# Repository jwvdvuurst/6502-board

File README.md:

# 6502-board

A W65C02S computer board with bank-switched SRAM, a ROM monitor and Tiny BASIC,
and a Raspberry Pi Pico USB terminal bridge.

- [Board design and hardware status](DESIGN.md)
- [ROM build, monitor commands, and BASIC](firmware/README.md)
- [Pico C firmware, build, and wiring](pico/README.md)
- [ROM/Pico interface contract](firmware/PROTOCOL.md)
- [Electrical schematic PDF](6502-electrical-draft.pdf)

The hardware is an electrical draft, not fabrication-ready. ROM firmware has
been tested in emulation. Pico C firmware builds to UF2 and passes portable
tests; physical hardware and USB/GPIO integration remain to be validated.

# Agents

Agents must follow the rules, references, skills and agents described in the [AI-hub](C:\Users\JWvdV\Documents\workspace\AI-hub) when this is available.
See also [AGENTS.md](AGENTS.md).

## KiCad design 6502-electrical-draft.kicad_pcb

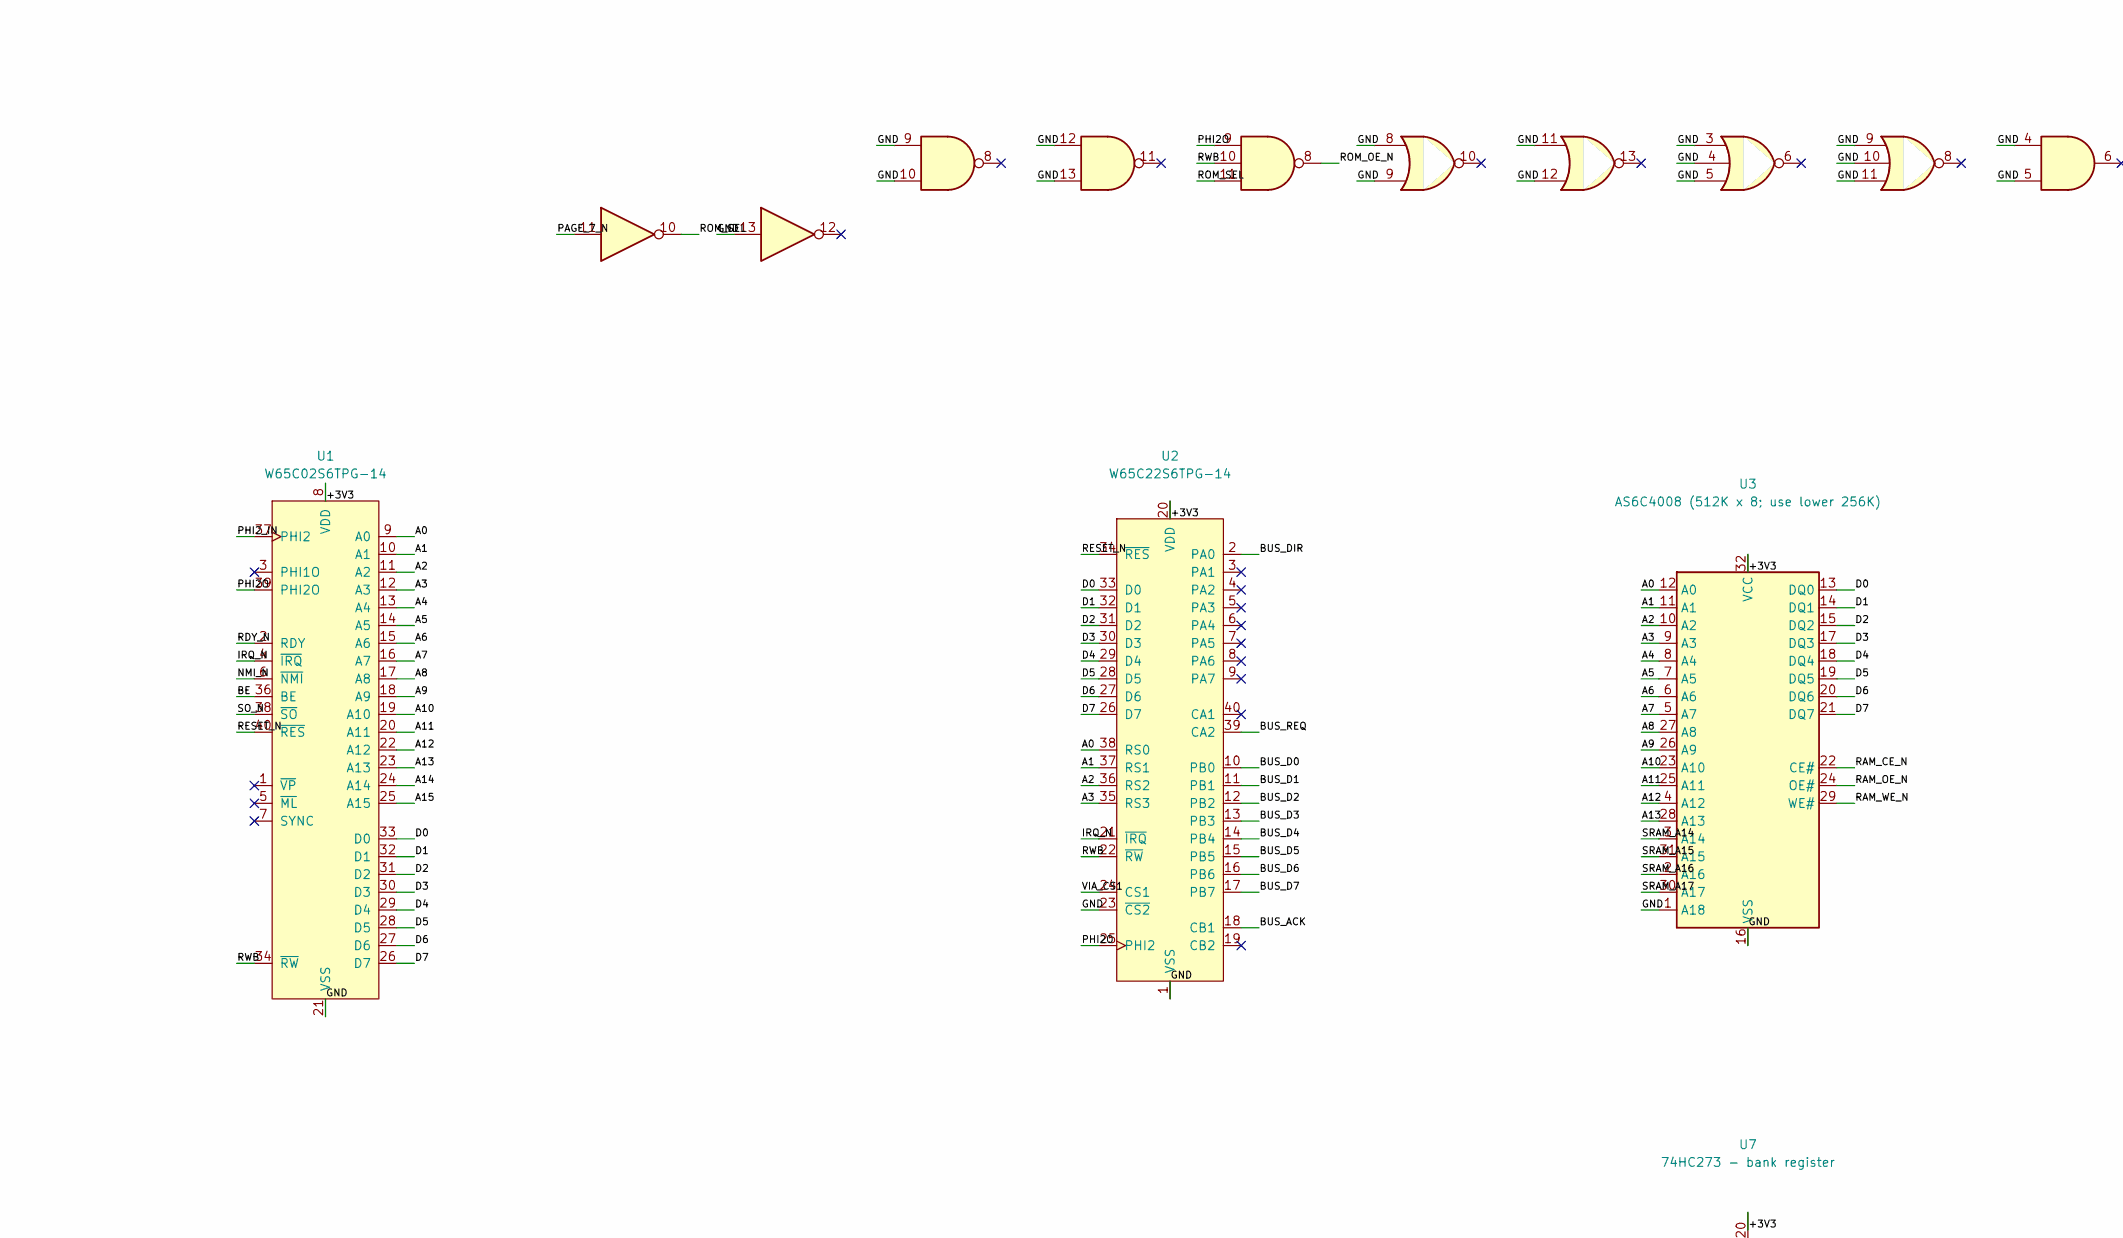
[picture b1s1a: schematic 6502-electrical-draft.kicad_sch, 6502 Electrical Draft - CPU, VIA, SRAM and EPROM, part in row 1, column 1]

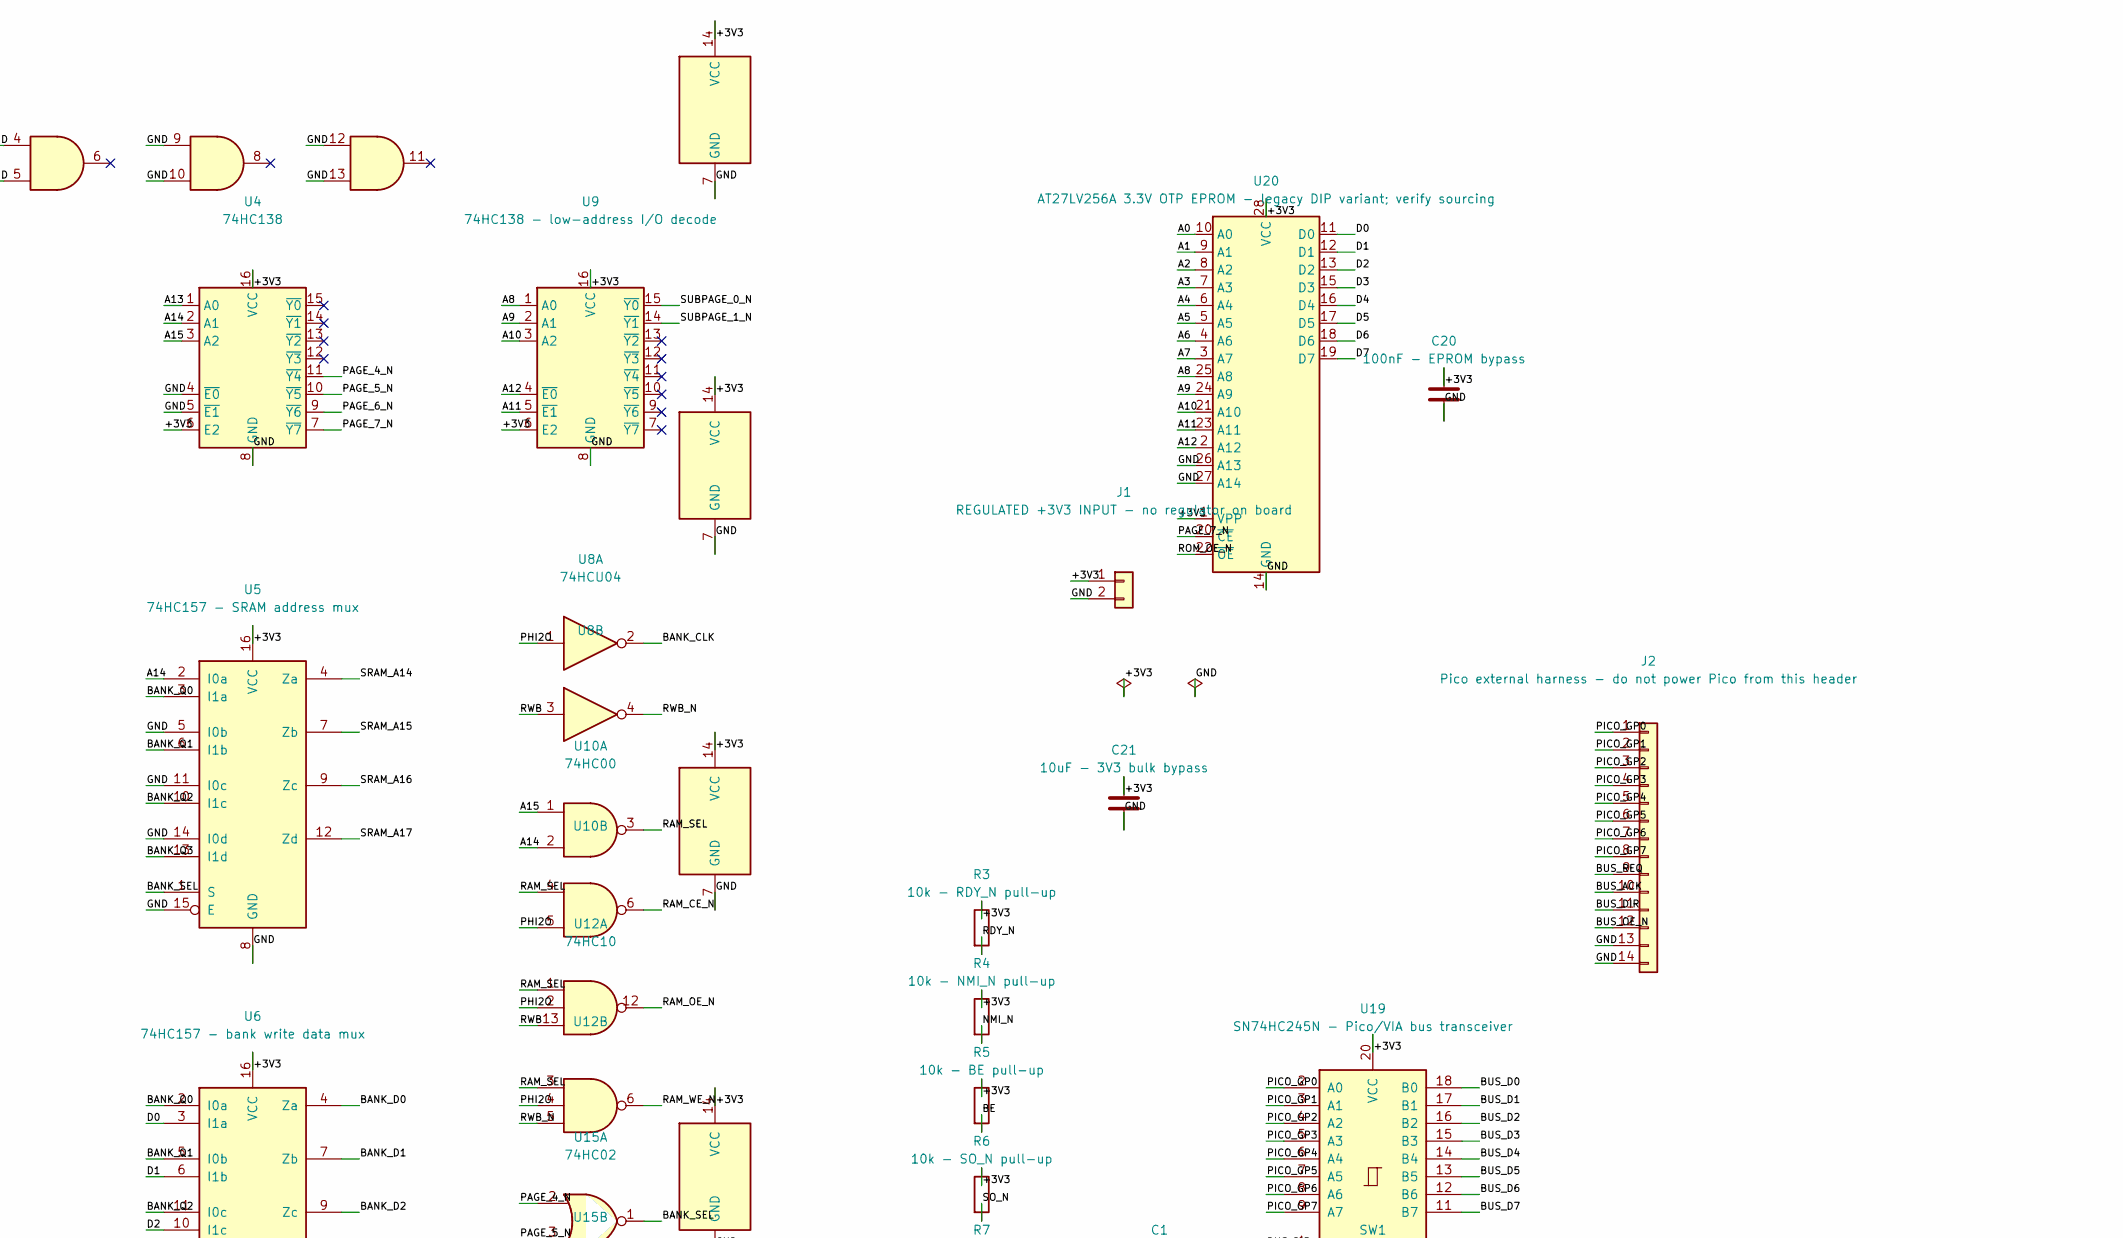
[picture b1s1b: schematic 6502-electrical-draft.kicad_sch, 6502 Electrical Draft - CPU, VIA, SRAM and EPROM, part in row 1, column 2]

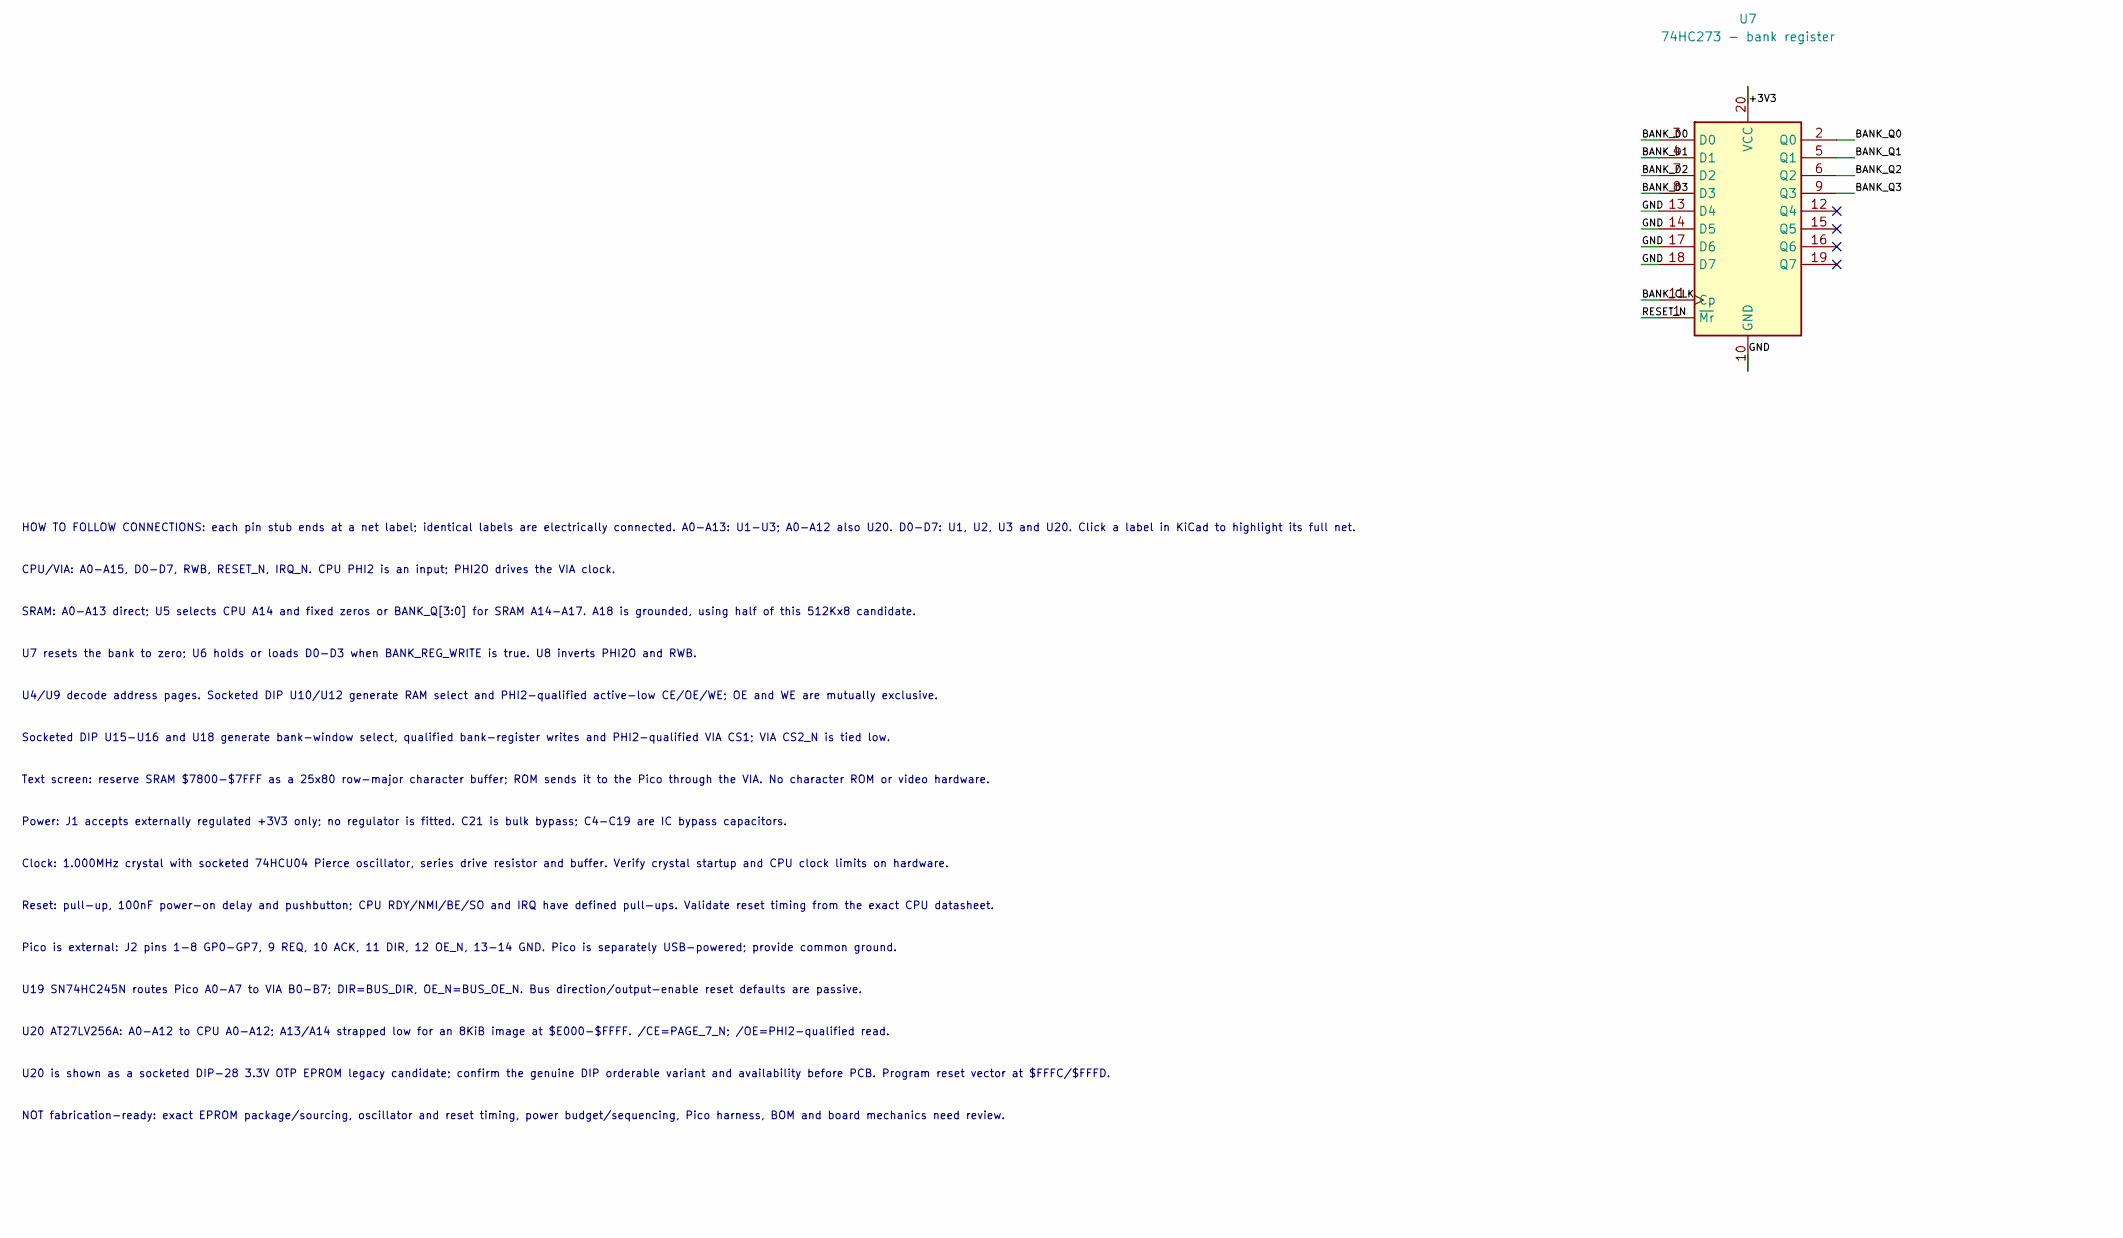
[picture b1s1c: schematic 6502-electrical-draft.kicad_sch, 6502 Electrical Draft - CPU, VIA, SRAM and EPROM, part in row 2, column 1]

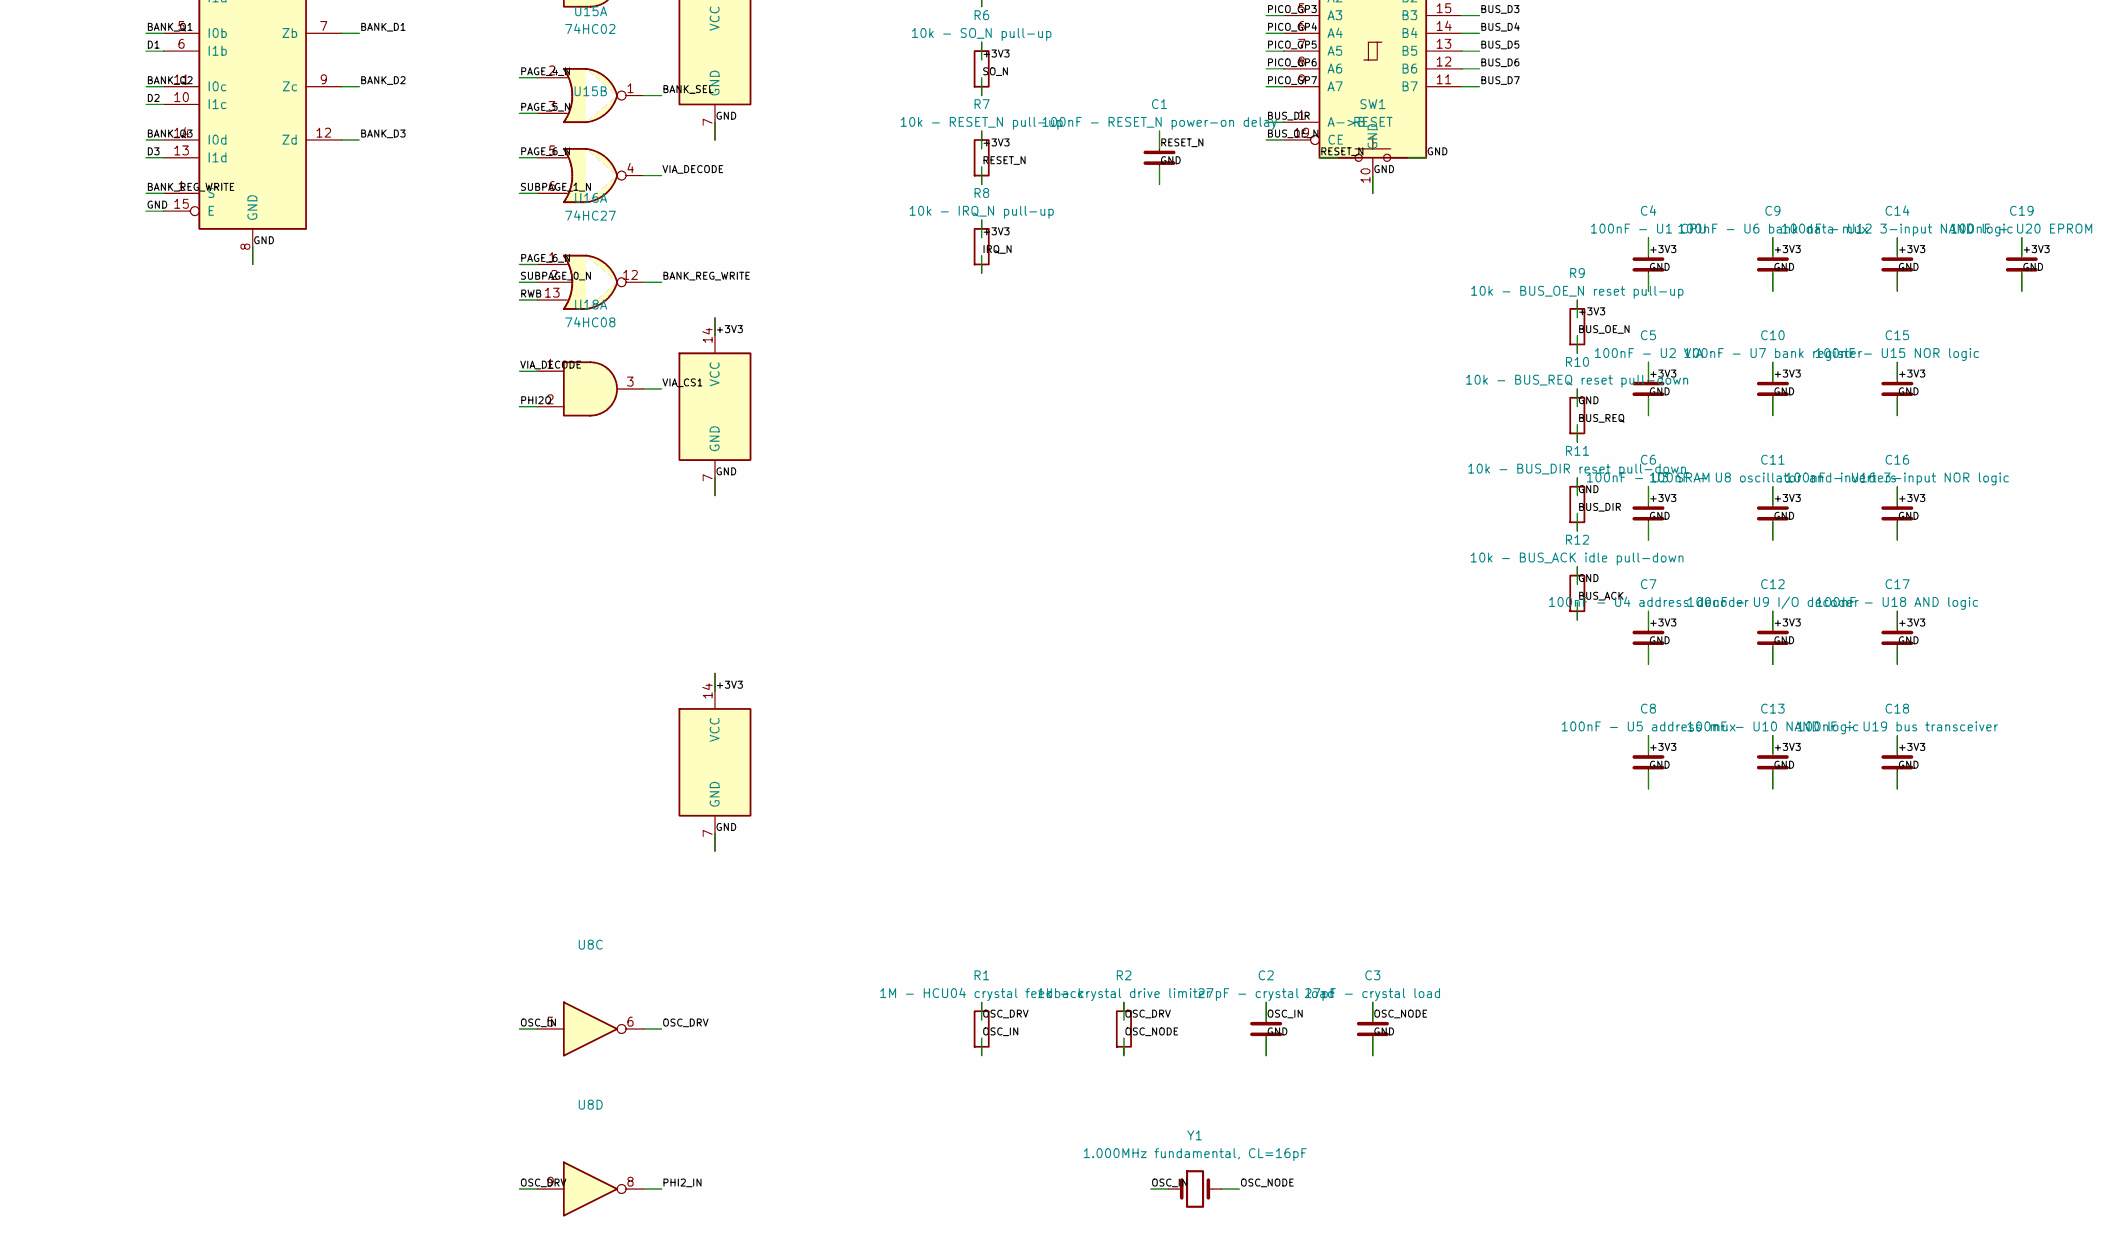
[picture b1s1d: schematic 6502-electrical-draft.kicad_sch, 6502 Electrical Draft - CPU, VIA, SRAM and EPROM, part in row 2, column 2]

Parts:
C1: 100nF - RESET_N power-on delay; C_Disc_D5.0mm_W2.5mm_P5.00mm
C2, C3: 27pF - crystal load; C_Disc_D5.0mm_W2.5mm_P5.00mm
C4: 100nF - U1 CPU; C_Disc_D5.0mm_W2.5mm_P5.00mm
C5: 100nF - U2 VIA; C_Disc_D5.0mm_W2.5mm_P5.00mm
C6: 100nF - U3 SRAM; C_Disc_D5.0mm_W2.5mm_P5.00mm
C7: 100nF - U4 address decoder; C_Disc_D5.0mm_W2.5mm_P5.00mm
C8: 100nF - U5 address mux; C_Disc_D5.0mm_W2.5mm_P5.00mm
C9: 100nF - U6 bank data mux; C_Disc_D5.0mm_W2.5mm_P5.00mm
C10: 100nF - U7 bank register; C_Disc_D5.0mm_W2.5mm_P5.00mm
C11: 100nF - U8 oscillator and inverters; C_Disc_D5.0mm_W2.5mm_P5.00mm
C12: 100nF - U9 I/O decoder; C_Disc_D5.0mm_W2.5mm_P5.00mm
C13: 100nF - U10 NAND logic; C_Disc_D5.0mm_W2.5mm_P5.00mm
C14: 100nF - U12 3-input NAND logic; C_Disc_D5.0mm_W2.5mm_P5.00mm
C15: 100nF - U15 NOR logic; C_Disc_D5.0mm_W2.5mm_P5.00mm
C16: 100nF - U16 3-input NOR logic; C_Disc_D5.0mm_W2.5mm_P5.00mm
C17: 100nF - U18 AND logic; C_Disc_D5.0mm_W2.5mm_P5.00mm
C18: 100nF - U19 bus transceiver; C_Disc_D5.0mm_W2.5mm_P5.00mm
C19: 100nF - U20 EPROM; C_Disc_D5.0mm_W2.5mm_P5.00mm
C20: 100nF - EPROM bypass; C_Disc_D5.0mm_W2.5mm_P5.00mm
C21: 10uF - 3V3 bulk bypass; C_Disc_D5.0mm_W2.5mm_P5.00mm
J1: REGULATED +3V3 INPUT - no regulator on board; PinHeader_1x02_P2.54mm_Vertical
J2: Pico external harness - do not power Pico from th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; PinHeader_1x14_P2.54mm_Vertical
R1: 1M - HCU04 crystal feedback; R_Axial_DIN0207_L6.3mm_D2.5mm_P7.62mm_Horizontal
R2: 1k - crystal drive limiter; R_Axial_DIN0207_L6.3mm_D2.5mm_P7.62mm_Horizontal
R3: 10k - RDY_N pull-up; R_Axial_DIN0207_L6.3mm_D2.5mm_P7.62mm_Horizontal
R4: 10k - NMI_N pull-up; R_Axial_DIN0207_L6.3mm_D2.5mm_P7.62mm_Horizontal
R5: 10k - BE pull-up; R_Axial_DIN0207_L6.3mm_D2.5mm_P7.62mm_Horizontal
R6: 10k - SO_N pull-up; R_Axial_DIN0207_L6.3mm_D2.5mm_P7.62mm_Horizontal
R7: 10k - RESET_N pull-up; R_Axial_DIN0207_L6.3mm_D2.5mm_P7.62mm_Horizontal
R8: 10k - IRQ_N pull-up; R_Axial_DIN0207_L6.3mm_D2.5mm_P7.62mm_Horizontal
R9: 10k - BUS_OE_N reset pull-up; R_Axial_DIN0207_L6.3mm_D2.5mm_P7.62mm_Horizontal
R10: 10k - BUS_REQ reset pull-down; R_Axial_DIN0207_L6.3mm_D2.5mm_P7.62mm_Horizontal
R11: 10k - BUS_DIR reset pull-down; R_Axial_DIN0207_L6.3mm_D2.5mm_P7.62mm_Horizontal
R12: 10k - BUS_ACK idle pull-down; R_Axial_DIN0207_L6.3mm_D2.5mm_P7.62mm_Horizontal
SW1: RESET; SW_PUSH_6mm
U1: W65C02S6TPG-14; DIP-40_W15.24mm_Socket
U2: W65C22S6TPG-14; DIP-40_W15.24mm_Socket
U3: AS6C4008 (512K x 8; use lower 256K); DIP-32_W15.24mm_Socket
U4: 74HC138; DIP-16_W7.62mm_Socket
U5: 74HC157 - SRAM address mux; DIP-16_W7.62mm_Socket
U6: 74HC157 - bank write data mux; DIP-16_W7.62mm_Socket
U7: 74HC273 - bank register; DIP-20_W7.62mm_Socket
U8: 74HCU04; DIP-14_W7.62mm_Socket
U9: 74HC138 - low-address I/O decode; DIP-16_W7.62mm_Socket
U10: 74HC00; DIP-14_W7.62mm_Socket
U12: 74HC10; DIP-14_W7.62mm_Socket
U15: 74HC02; DIP-14_W7.62mm_Socket
U16: 74HC27; DIP-14_W7.62mm_Socket
U18: 74HC08; DIP-14_W7.62mm_Socket
U19: SN74HC245N - Pico/VIA bus transceiver; DIP-20_W7.62mm_Socket
U20: AT27LV256A 3.3V OTP EPROM - legacy DIP variant; v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; DIP-28_W15.24mm_Socket
Y1: 1.000MHz fundamental, CL=16pF; Crystal_HC49-U_Vertical

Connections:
/+3V3: C4.1, C5.1, C6.1, C7.1, C8.1, C9.1, C10.1, C11.1, C12.1, C13.1, C14.1, C15.1, C16.1, C17.1, C18.1, C19.1, C20.1, C21.1, J1.1, R3.1, R4.1, R5.1, R6.1, R7.1, R8.1, R9.1, U1.8 (VDD), U2.20 (VDD), U3.32 (VCC), U4.6 (E2), U4.16 (VCC), U5.16 (VCC), U6.16 (VCC), U7.20 (VCC), U8.14 (VCC), U9.6 (E2), U9.16 (VCC), U10.14 (VCC), U12.14 (VCC), U15.14 (VCC), U16.14 (VCC), U18.14 (VCC), U19.20 (VCC), U20.1 (VPP), U20.28 (VCC)
/A0: U1.9 (A0), U2.38 (RS0), U3.12 (A0), U20.10 (A0)
/A1: U1.10 (A1), U2.37 (RS1), U3.11 (A1), U20.9 (A1)
/A2: U1.11 (A2), U2.36 (RS2), U3.10 (A2), U20.8 (A2)
/A3: U1.12 (A3), U2.35 (RS3), U3.9 (A3), U20.7 (A3)
/A4: U1.13 (A4), U3.8 (A4), U20.6 (A4)
/A5: U1.14 (A5), U3.7 (A5), U20.5 (A5)
/A6: U1.15 (A6), U3.6 (A6), U20.4 (A6)
/A7: U1.16 (A7), U3.5 (A7), U20.3 (A7)
/A8: U1.17 (A8), U3.27 (A8), U9.1 (A0), U20.25 (A8)
/A9: U1.18 (A9), U3.26 (A9), U9.2 (A1), U20.24 (A9)
/A10: U1.19 (A10), U3.23 (A10), U9.3 (A2), U20.21 (A10)
/A11: U1.20 (A11), U3.25 (A11), U9.5 (~E1), U20.23 (A11)
/A12: U1.22 (A12), U3.4 (A12), U9.4 (~E0), U20.2 (A12)
/A13: U1.23 (A13), U3.28 (A13), U4.1 (A0)
/A14: U1.24 (A14), U4.2 (A1), U5.2 (I0a), U10.2
/A15: U1.25 (A15), U4.3 (A2), U10.1
/BANK_CLK: U7.11 (Cp), U8.2
/BANK_D0: U6.4 (Za), U7.3 (D0)
/BANK_D1: U6.7 (Zb), U7.4 (D1)
/BANK_D2: U6.9 (Zc), U7.7 (D2)
/BANK_D3: U6.12 (Zd), U7.8 (D3)
/BANK_Q0: U5.3 (I1a), U6.2 (I0a), U7.2 (Q0)
/BANK_Q1: U5.6 (I1b), U6.5 (I0b), U7.5 (Q1)
/BANK_Q2: U5.10 (I1c), U6.11 (I0c), U7.6 (Q2)
/BANK_Q3: U5.13 (I1d), U6.14 (I0d), U7.9 (Q3)
/BANK_REG_WRITE: U6.1 (S), U16.12
/BANK_SEL: U5.1 (S), U15.1
/BE: R5.2, U1.36 (BE)
/BUS_ACK: J2.10, R12.2, U2.18 (CB1)
/BUS_D0: U2.10 (PB0), U19.18 (B0)
/BUS_D1: U2.11 (PB1), U19.17 (B1)
/BUS_D2: U2.12 (PB2), U19.16 (B2)
/BUS_D3: U2.13 (PB3), U19.15 (B3)
/BUS_D4: U2.14 (PB4), U19.14 (B4)
/BUS_D5: U2.15 (PB5), U19.13 (B5)
/BUS_D6: U2.16 (PB6), U19.12 (B6)
/BUS_D7: U2.17 (PB7), U19.11 (B7)
/BUS_DIR: J2.11, R11.2, U2.2 (PA0), U19.1 (A->B)
/BUS_OE_N: J2.12, R9.2, U19.19 (CE)
/BUS_REQ: J2.9, R10.2, U2.39 (CA2)
/D0: U1.33 (D0), U2.33 (D0), U3.13 (DQ0), U6.3 (I1a), U20.11 (D0)
/D1: U1.32 (D1), U2.32 (D1), U3.14 (DQ1), U6.6 (I1b), U20.12 (D1)
/D2: U1.31 (D2), U2.31 (D2), U3.15 (DQ2), U6.10 (I1c), U20.13 (D2)
/D3: U1.30 (D3), U2.30 (D3), U3.17 (DQ3), U6.13 (I1d), U20.15 (D3)
/D4: U1.29 (D4), U2.29 (D4), U3.18 (DQ4), U20.16 (D4)
/D5: U1.28 (D5), U2.28 (D5), U3.19 (DQ5), U20.17 (D5)
/D6: U1.27 (D6), U2.27 (D6), U3.20 (DQ6), U20.18 (D6)
/D7: U1.26 (D7), U2.26 (D7), U3.21 (DQ7), U20.19 (D7)
/GND: C1.2, C2.2, C3.2, C4.2, C5.2, C6.2, C7.2, C8.2, C9.2, C10.2, C11.2, C12.2, C13.2, C14.2, C15.2, C16.2, C17.2, C18.2, C19.2, C20.2, C21.2, J1.2, J2.13, J2.14, R10.1, R11.1, R12.1, SW1.2, U1.21 (VSS), U2.1 (VSS), U2.23 (~CS2), U3.1 (A18), U3.16 (VSS), U4.4 (~E0), U4.5 (~E1), U4.8 (GND), U5.5 (I0b), U5.8 (GND), U5.11 (I0c), U5.14 (I0d), U5.15 (E), U6.8 (GND), U6.15 (E), U7.10 (GND), U7.13 (D4), U7.14 (D5), U7.17 (D6), U7.18 (D7), U8.7 (GND), U8.13, U9.8 (GND), U10.7 (GND), U10.9, U10.10, U10.12, U10.13, U12.7 (GND), U15.7 (GND), U15.8, U15.9, U15.11, U15.12, U16.3, U16.4, U16.5, U16.7 (GND), U16.9, U16.10, U16.11, U18.4, U18.5, U18.7 (GND), U18.9, U18.10, U18.12, U18.13, U19.10 (GND), U20.14 (GND), U20.26 (A13), U20.27 (A14)
/IRQ_N: R8.2, U1.4 (~IRQ), U2.21 (~IRQ)
/NMI_N: R4.2, U1.6 (~NMI)
/OSC_DRV: R1.1, R2.1, U8.6, U8.9
/OSC_IN: C2.1, R1.2, U8.5, Y1.1
/OSC_NODE: C3.1, R2.2, Y1.2
/PAGE_4_N: U4.11 (~Y4), U15.2
/PAGE_5_N: U4.10 (~Y5), U15.3
/PAGE_6_N: U4.9 (~Y6), U15.5, U16.1
/PAGE_7_N: U4.7 (~Y7), U8.11, U20.20 (~CE)
/PHI2O: U1.39 (PHI2O), U2.25 (PHI2), U8.1, U10.5, U12.2, U12.4, U12.9, U18.2
/PHI2_IN: U1.37 (PHI2), U8.8
/PICO_GP0: J2.1, U19.2 (A0)
/PICO_GP1: J2.2, U19.3 (A1)
/PICO_GP2: J2.3, U19.4 (A2)
/PICO_GP3: J2.4, U19.5 (A3)
/PICO_GP4: J2.5, U19.6 (A4)
/PICO_GP5: J2.6, U19.7 (A5)
/PICO_GP6: J2.7, U19.8 (A6)
/PICO_GP7: J2.8, U19.9 (A7)
/RAM_CE_N: U3.22 (CE#), U10.6
/RAM_OE_N: U3.24 (OE#), U12.12
/RAM_SEL: U10.3, U10.4, U12.1, U12.3
/RAM_WE_N: U3.29 (WE#), U12.6
/RDY_N: R3.2, U1.2 (RDY)
/RESET_N: C1.1, R7.2, SW1.1, U1.40 (~RES), U2.34 (~RES), U7.1 (~Mr)
/ROM_OE_N: U12.8, U20.22 (~OE)
/ROM_SEL: U8.10, U12.11
/RWB: U1.34 (~RW), U2.22 (~RW), U8.3, U12.10, U12.13, U16.13
/RWB_N: U8.4, U12.5
/SO_N: R6.2, U1.38 (~SO)
/SRAM_A14: U3.3 (A14), U5.4 (Za)
/SRAM_A15: U3.31 (A15), U5.7 (Zb)
/SRAM_A16: U3.2 (A16), U5.9 (Zc)
/SRAM_A17: U3.30 (A17), U5.12 (Zd)
/SUBPAGE_0_N: U9.15 (~Y0), U16.2
/SUBPAGE_1_N: U9.14 (~Y1), U15.6
/VIA_CS1: U2.24 (CS1), U18.3
/VIA_DECODE: U15.4, U18.1

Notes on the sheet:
HOW TO FOLLOW CONNECTIONS: each pin stub ends at a net label; identical labels are electrically connected. A0-A13: U1-U3; A0-A12 also U20. D0-D7: U1, U2, U3 and U20. Click a label in KiCad to highlight its full net.
CPU/VIA: A0-A15, D0-D7, RWB, RESET_N, IRQ_N. CPU PHI2 is an input; PHI2O drives the VIA clock.
SRAM: A0-A13 direct; U5 selects CPU A14 and fixed zeros or BANK_Q[3:0] for SRAM A14-A17. A18 is grounded, using half of this 512Kx8 candidate.
U7 resets the bank to zero; U6 holds or loads D0-D3 when BANK_REG_WRITE is true. U8 inverts PHI2O and RWB.
U4/U9 decode address pages. Socketed DIP U10/U12 generate RAM select and PHI2-qualified active-low CE/OE/WE; OE and WE are mutually exclusive.
Socketed DIP U15-U16 and U18 generate bank-window select, qualified bank-register writes and PHI2-qualified VIA CS1; VIA CS2_N is tied low.
Text screen: reserve SRAM $7800-$7FFF as a 25x80 row-major character buffer; ROM sends it to the Pico through the VIA. No character ROM or video hardware.
Power: J1 accepts externally regulated +3V3 only; no regulator is fitted. C21 is bulk bypass; C4-C19 are IC bypass capacitors.
Clock: 1.000MHz crystal with socketed 74HCU04 Pierce oscillator, series drive resistor and buffer. Verify crystal startup and CPU clock limits on hardware.
Reset: pull-up, 100nF power-on delay and pushbutton; CPU RDY/NMI/BE/SO and IRQ have defined pull-ups. Validate reset timing from the exact CPU datasheet.
Pico is external: J2 pins 1-8 GP0-GP7, 9 REQ, 10 ACK, 11 DIR, 12 OE_N, 13-14 GND. Pico is separately USB-powered; provide common ground.
U19 SN74HC245N routes Pico A0-A7 to VIA B0-B7; DIR=BUS_DIR, OE_N=BUS_OE_N. Bus direction/output-enable reset defaults are passive.
U20 AT27LV256A: A0-A12 to CPU A0-A12; A13/A14 strapped low for an 8KiB image at $E000-$FFFF. /CE=PAGE_7_N; /OE=PHI2-qualified read.
U20 is shown as a socketed DIP-28 3.3V OTP EPROM legacy candidate; confirm the genuine DIP orderable variant and availability before PCB. Program reset vector at $FFFC/$FFFD.
NOT fabrication-ready: exact EPROM package/sourcing, oscillator and reset timing, power budget/sequencing, Pico harness, BOM and board mechanics need review.

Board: 2 copper layers, 53 parts (0 on the bottom side), 88 nets, no tracks yet.

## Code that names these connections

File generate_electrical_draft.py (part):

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        "~{RES}": "RESET_N",
        "CA2": "BUS_REQ",
        "CB1": "BUS_ACK",
        "PA0": "BUS_DIR",
        "CA1": None,
        "CB2": None,
        **{f"PA{i}": None for i in range(1, 8)},
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
logic_units = [
    ("74HCU04", "U8", 1, logic_x, 88.9, "BANK_CLK inverter", {
        "PIN1": "PHI2O", "PIN2": "BANK_CLK",
    }),
    ("74HCU04", "U8", 2, logic_x, 99.06, "RWB inverter", {
        "PIN3": "RWB", "PIN4": "RWB_N",
    }),
    ("74HCU04", "U8", 3, 388.62, 304.8, "1 MHz crystal oscillator", {
        "PIN5": "OSC_IN", "PIN6": "OSC_DRV",
    }),
    ("74HCU04", "U8", 4, 388.62, 327.66, "PHI2 clock buffer", {
        "PIN9": "OSC_DRV", "PIN8": "PHI2_IN",
    }),
    ("74HC00", "U10", 1, logic_x, 115.57, "RAM range", {
        "PIN1": "A15", "PIN2": "A14", "PIN3": "RAM_SEL",
    }),
    ("74HC00", "U10", 2, logic_x, 127.0, "RAM /CE", {
        "PIN4": "RAM_SEL", "PIN5": "PHI2O", "PIN6": "RAM_CE_N",
    }),
    ("74HC10", "U12", 1, logic_x, 140.97, "RAM /OE", {
        "PIN1": "RAM_SEL", "PIN2": "PHI2O", "PIN13": "RWB", "PIN12": "RAM_OE_N",
    }),
    ("74HC10", "U12", 2, logic_x, 154.94, "RAM /WE", {
        "PIN3": "RAM_SEL", "PIN4": "PHI2O", "PIN5": "RWB_N", "PIN6": "RAM_WE_N",
    }),
    ("74HC02", "U15", 1, logic_x, 171.45, "bank-window select", {
        "PIN1": "BANK_SEL", "PIN2": "PAGE_4_N", "PIN3": "PAGE_5_N",
    }),
    ("74HC02", "U15", 2, logic_x, 182.88, "VIA address select", {
        "PIN4": "VIA_DECODE", "PIN5": "PAGE_6_N", "PIN6": "SUBPAGE_1_N",
    }),
    ("74HC27", "U16", 1, logic_x, 198.12, "bank-register write select", {
        "PIN1": "PAGE_6_N", "PIN2": "SUBPAGE_0_N", "PIN13": "RWB",
        "PIN12": "BANK_REG_WRITE",
    }),
    ("74HC08", "U18", 1, logic_x, 213.36, "VIA phase enable", {
        "PIN1": "VIA_DECODE", "PIN2": "PHI2O", "PIN3": "VIA_CS1",
    }),
]
logic_unused_units = [
    ("74HCU04", "U8", 5, 106.68, 30.48, {
        "PIN11": "PAGE_7_N", "PIN10": "ROM_SEL",
    }),
    ("74HCU04", "U8", 6, 129.54, 30.48, {"PIN13": "GND", "PIN12": None}),
    ("74HC00", "U10", 3, 152.4, 20.32, {"PIN8": None, "PIN9": "GND", "PIN10": "GND"}),
    ("74HC00", "U10", 4, 175.26, 20.32, {"PIN11": None, "PIN12": "GND", "PIN13": "GND"}),
    ("74HC10", "U12", 3, 198.12, 20.32, {
        "PIN8": "ROM_OE_N",
        "PIN9": "PHI2O",
        "PIN10": "RWB",
        "PIN11": "ROM_SEL",
    }),
    ("74HC02", "U15", 3, 220.98, 20.32, {"PIN8": "GND", "PIN9": "GND", "PIN10": None}),
    ("74HC02", "U15", 4, 243.84, 20.32, {"PIN11": "GND", "PIN12": "GND", "PIN13": None}),
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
